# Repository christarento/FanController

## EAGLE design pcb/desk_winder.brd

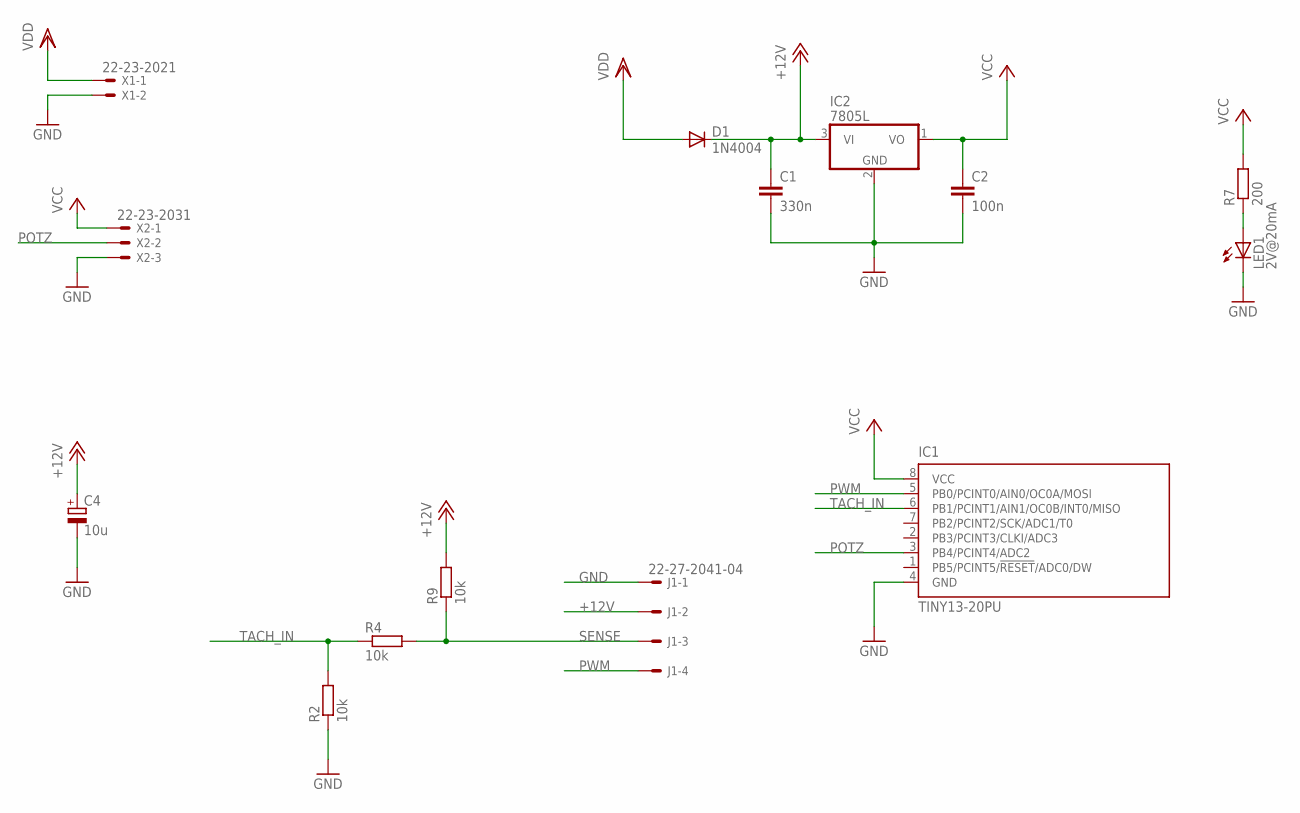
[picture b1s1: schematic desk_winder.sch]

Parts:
C1: 330n; C050-025X075
C2: 100n; C050-025X075
C4: 10u; E2,5-6
D1: 1N4004; DO41-10
IC1: TINY13-20PU; DIL08
IC2: 7805L; TO92
J1: 22-27-2041-04; 6410-04
LED1: 2V@20mA; LED5MM
R2, R4, R9: 10k; 0207/12
R7: 200; 0207/12
X1: 22-23-2021
X2: 22-23-2031

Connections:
+12V: C1.1, C4.+, D1.C, IC2.3 (VI), J1.2, R9.2
GND: C1.2, C2.2, C4.-, IC1.4 (GND), IC2.2 (GND), J1.1, LED1.K (C), R2.1, X1.2, X2.3
unnamed: LED1.A, R7.1
POTZ: IC1.3 (PB4/PCINT4/ADC2), X2.2
PWM: IC1.5 (PB0/PCINT0/AIN0/OC0A/MOSI), J1.4
SENSE: J1.3, R4.2, R9.1
TACH_IN: IC1.6 (PB1/PCINT1/AIN1/OC0B/INT0/MISO), R2.2, R4.1
VCC: C2.1, IC1.8 (VCC), IC2.1 (VO), R7.2, X2.1
VDD: D1.A, X1.1

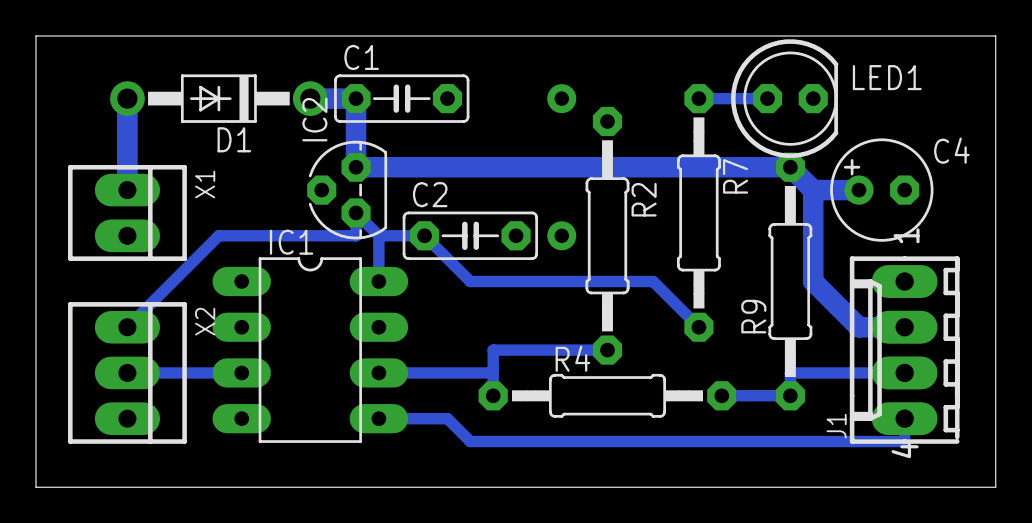
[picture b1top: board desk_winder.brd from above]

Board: 2 copper layers, 53.3 x 25.1 mm, 14 parts (0 on the bottom side), 9 nets.

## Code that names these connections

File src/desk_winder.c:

/*
 * Fan Controller
 * Copyright (C) 2014  Christopher Tarento
 *
 * This program is free software; you can redistribute it and/or modify
 * it under the terms of the GNU General Public License as published by
 * the Free Software Foundation; either version 2 of the License, or
 * (at your option) any later version.
 *
 * This program is distributed in the hope that it will be useful,
 * but WITHOUT ANY WARRANTY; without even the implied warranty of
 * MERCHANTABILITY or FITNESS FOR A PARTICULAR PURPOSE.  See the
 * GNU General Public License for more details.
 *
 * You should have received a copy of the GNU General Public License along
 * with this program; if not, write to the Free Software Foundation, Inc.,
 * 51 Franklin Street, Fifth Floor, Boston, MA 02110-1301 USA.
 */ 

#define F_CPU 4800000UL
#define F_PWM 18750UL

#include <limits.h>

#include <avr/interrupt.h>
#include <avr/io.h>
#include <util/atomic.h>


//------------ DEFINES
#define TRUE 1
#define FALSE 0
#define STARTUP_PWM 200
#define STARTUP_TIME (F_PWM * 2)
#define STALL_THRESHOLD_TIME (F_PWM / 2)
#define STALL_RETRY_TIME (F_PWM * 2)
#define MIN_PWM_DUTY 40

//------------ FUSES
//- high byte -> 0xff

//- low byte -> 0x79
//CKDIV8[0] 1 : Clock divider -> NO
//SUT[1:0] 10 : Start-up times -> Slowly rising time
//CKSEL[1:0] 01 Internal RC Oscillator -> 4.8 MHz

//------------ I/O
//PB0 (OC0A) PWM control @21-28KHz output
//PB1 (INT0) tach input two pulses by revolution
//PB4 (ADC2) potz input
#define CTRL_PIN 0
#define TACH_PIN 1
#define POTZ_PIN (1<<MUX1)


//! count time since last sensor signal
volatile uint32_t g_stall_time = 0;
//! used to measure time
volatile uint32_t g_time_counter = 0;

/*! \brief Flags for motor state
 * uses C bit fields
 */
volatile struct
{
	//! true when motor stalled
	uint8_t stall : 1;
	//! true when starting motor
	uint8_t starting : 1;
	//! padding to 8 bits
	uint8_t : 6;
} g_fan = {FALSE, FALSE};


/*! \brief Pin Change Interrupt vector
 */
ISR(PCINT0_vect)
{
	// reset time since last sensor change
	g_stall_time = 0;
}

/*! \brief Timer 0 Overflow Interrupt vector
 */
ISR(TIM0_OVF_vect)
{
	// increment time counter as long as not overflowing
	if (g_time_counter < UINT32_MAX)
	{
		++g_time_counter;
	}

	// increment as long as not at stall limit, otherwise raise stall flag
	if (g_stall_time < STALL_THRESHOLD_TIME)
	{
		++g_stall_time;
	}
	else
	{
		g_fan.stall = TRUE;
	}
	
	// check fan startup end
	if (g_fan.starting == TRUE && g_time_counter > STARTUP_TIME)
	{
		// fan has finished its startup phase
		g_fan.starting = FALSE;
	}
}


/*! \brief init clock, adc, pwm ...
 */
inline void init(void)
{
	//== PORT configuration
	//CTRL_PIN direction as output
	DDRB = (1<<CTRL_PIN);

	//== Pin change Interrupt
	PCMSK = (1<<TACH_PIN);//pin change mask register, activate TACH_PIN
	GIMSK = (1<<PCIE);//pin change interrupt enable
	
	//== TIMER / PWM configuration
	// fast PWM, prescaler 1, Fpwm = F_CPU / (prescaler*256) -> 18750Hz
	TCCR0A = (1<<WGM01) | (1<<WGM00);//set OC0A at TOP, Fast PWM with TOP=0xff
	TCCR0B = (1<<CS00);//no prescaler (1)
	TCNT0 = 0;//Timer/Counter register to 0
	TIMSK0 = (1<<TOIE0);//Timer/Counter0 Overflow Interrupt Enable
		
	//== Analog to Digital Converter configuration
	// prescaler of ADC clock to 128 and enable ADC
	ADCSRA = (1<<ADPS2) | (1<<ADPS1) | (1<<ADPS0) | (1<<ADEN);
	// VCC as ref, left adjusted reading, POTZ_PIN as input (secured by mask)
	ADMUX = (0<<REFS0) | (1<<ADLAR) | (0b0011 & POTZ_PIN);
		
	//== Global interrupt
	sei();
}

/*! \brief Reads ADC input
 * \return read value 0-255
 */
uint8_t potzRead(void)
{
    // clear ADIF (write logical 1 to store 0) and start single conversion
    ADCSRA |= (1 << ADIF) | (1 << ADSC);
    // wait for conversion done -> ADIF flag active
    while (!(ADCSRA & (1 << ADIF)));
    // read out ADCH register
    return ADCH;
}

inline void setPower(uint8_t a_duty_cycle)
{
	if (a_duty_cycle == 0)
	{
		// PWM generator cannot give pure 0% duty cycle -> 1 clock cycle narrow spike 
		// we disconnect PWM generator and set output to 0 by hand
		TCCR0A &= ~(1<<COM0A1);
		PORTB &= ~(1<<CTRL_PIN);
	}
	else
	{
		// set PWM generator duty cycle
		OCR0A = a_duty_cycle;
		TCCR0A |= (1<<COM0A1);//clear OC0A on Compare Match
	}
}

/*! \brief Startup Pulse
 * Increase PWM value (if needed) for a short period of time to ensure that fan is starting
 * \param a_duty Preferred duty cycle. It can be increased to STARTUP_PWM for a short period
 */ 
void startFan(uint8_t a_duty)
{
	if (a_duty < STARTUP_PWM)
	{
		a_duty = STARTUP_PWM;
	}
	
	ATOMIC_BLOCK(ATOMIC_FORCEON)
	{
		g_fan.stall = FALSE;
		g_fan.starting = TRUE;
		g_stall_time = 0;
		g_time_counter = 0;
	}
	setPower(a_duty);
}

/*! \brief main
 */
int main(void)
{
	//! temporary duty value
	uint8_t duty;
	//! temporary time counter
	uint32_t time_counter;
	
	init();
	startFan(potzRead());
	
    while (1)
    {
        duty = potzRead();
		if (duty < MIN_PWM_DUTY)
		{
			duty = MIN_PWM_DUTY;
		}
		
		// do not update power when starting
		if (g_fan.starting == FALSE)
		{
			setPower(duty);
		}
		
		// stalled rotor : power off, wait and restart
		if (g_fan.stall == TRUE)
		{
			// power off
			setPower(0);
			
			// reset time counter
			ATOMIC_BLOCK(ATOMIC_FORCEON)
			{
				g_time_counter = 0;
			}
			
			// wait until delay finished
			do
			{
				ATOMIC_BLOCK(ATOMIC_FORCEON)
				{
					time_counter = g_time_counter;
				}
			}
			while (time_counter <= STALL_RETRY_TIME);
	
			// start up the fan again
			startFan(duty);
		}
    }
}

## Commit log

2014-01-23 solution / project creation
2014-01-23 * remove atsuo file * improve compilation warnings
2014-01-30 PCB first try
2014-08-13 WIP from AVR442
2014-08-13 part file
2014-08-13 AVR442 source code
2014-08-13 force output low when duty_cycle is 0
2014-08-17 CAD files for grid and fan support
2014-08-17 mininmum PWM to 20%
2014-08-20 add blade master 80 product sheet
2014-08-21 times tuning
2014-08-26 cosmetic
2014-10-04 remove empty README file
2014-10-04 insert license header
